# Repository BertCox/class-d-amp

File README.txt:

File: README.txt
Description: Project-specific instructions and information concerning files
    located within this hierarchy and subhierarchies. In the event of
    conflicts, the lowest-level README.txt file is used for information
    regarding a file or files.

Current Location: ClassDAmp/

Description:
    The Class-D Audio amplifier is an audio amplifier based on the 2004 Sorensen
audio amplifier design (http://listen.to/audioexperiment). The amplifier is able
to provide 100 watts RMS power spread across 2 stereo channels (50 watts RMS each)

Contents:
    Included in this repository are the source files and documentation
necessary to recreate the Class-D audio amplifier. If you believe something is 
missing from the project, please contact us at http://nbitwonder.com/blog/contact

Documentation:
    Documentation related to this project is included in the 'Documentation'
folder. For additional documentation and other information, please see:
http://nbitwonder.com/blog/projects/class-d-audio-amp/

License Information:
    NBitWonder projects are released under the GNU GPL v3.0 for software,
firmware, simulations, and documentation and Creative Commons CC-BY-3.0 
for electronics and mechanical components. License copies can be found in the
file 'license.txt' in each of these top-level folders.
    NBitWonder projects may use files, software, libraries, etc. which is not
open source. These components may not be distributed within the project
repository or use a different license than that specified in license.txt. In
these cases, acquisition instructions and license exceptions are noted in a
given hierarchy's 'README.txt' file. Where conflicting, the lowest-level
'README.txt' file shall apply to a given file or files.

Ben Laskowski
Chief Technical Officer
NBitWonder, LLC

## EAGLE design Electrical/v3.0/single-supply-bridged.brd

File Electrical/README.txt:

File: README.txt
Description: Project-specific instructions and information concerning files
    located within this hierarchy and subhierarchies. In the event of
    conflicts, the lowest-level README.txt file is used for information
    regarding a file or files.

Current Location: ClassDAmp/Electrical

Notes:
    This directory contains the following files:
    Version 3.0:
	* single-supply-bridged schematic and layout: The most recent version of 	  the circuit, and the only supported version.
    Version 2.0:
        * single-supply-bridged schematic and layout: 50W max output, questionable 	  speaker protection circuit
    Version 1.0:    
        * class-d-amp-single-supply schematic and pcb: An untested lower-output
          version, appx. 15W per channel
        * class-d-amp-3-5-mm sch/pcb: A dual-supply version, 25W per channel max.
          Not recommended for construction.
        * class-d-amp sch/pcb: The original board layout. Self-destructed during
          first test. Do not build.

Software:
    All electronic design files were created using EagleCAD v5.11 from CADSoft. 
A freeware copy of this software, as well as additional information about this 
software, can be found at http://www.cadsoftusa.com/

License:
    All electronic CAD design files contained within this hierarchy, except those
noted in the 'Exceptions' section below, are made publicly available via a 
Creative-Commons CC-BY-SA 3.0 license. For more information on the license, see 
http://creativecommons.org/licenses/by-sa/3.0/
    Additionally, a complete copy of the license text can be found in the file
'license.txt' distributed within this folder.

Exceptions:
    The following alternative licensing requirements apply to the following files:

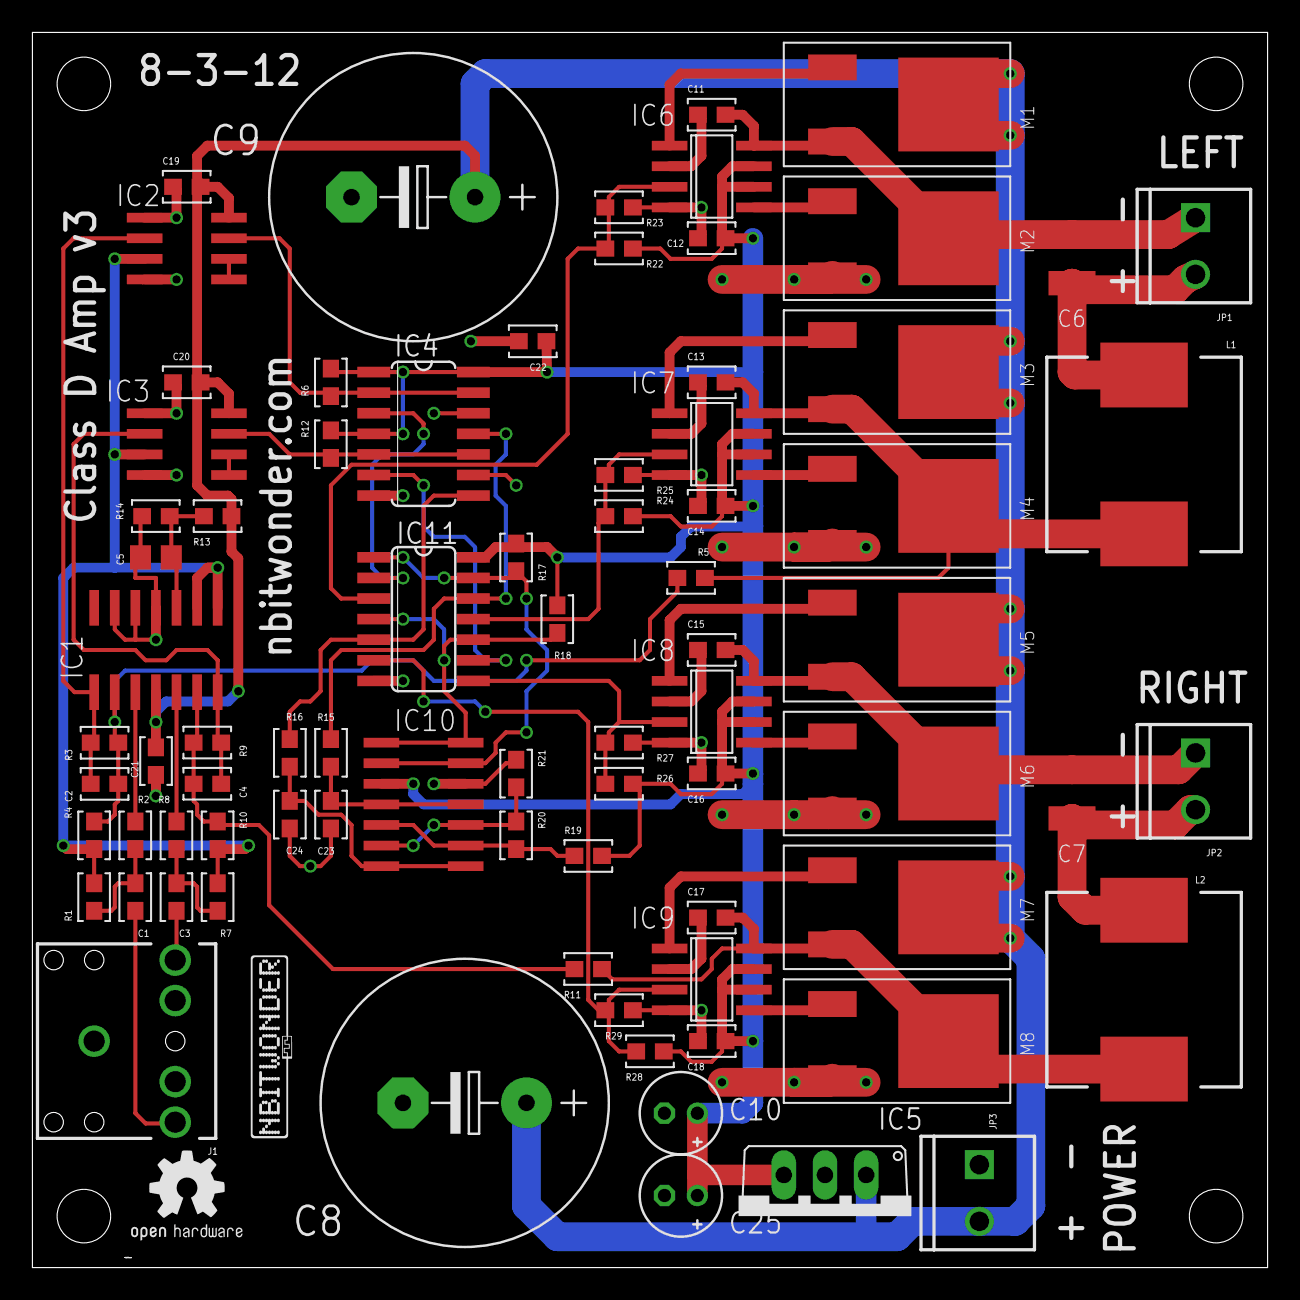
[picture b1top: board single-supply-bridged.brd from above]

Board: 2 copper layers, 76.2 x 76.2 mm, 85 parts (0 on the bottom side), 51 nets.

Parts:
C1, C3, C11, C13, C15, C17: 1u; 0603
C2, C4, C23, C24: 820p; 0603
C5: 10u; C0805
C6, C7: 270n; C1210K
C8, C9: 3300u; E7,5-18
C10, C25: 100u; E2-5
C12, C14, C16, C18, C19, C20, C21, C22: 100n; 0603
GOLD_ORB_SM1: OSHWLOGO_GOLD_ORB_SM; OSHW2
IC1: TL084D; SO14
IC2, IC3: LM311D; SO08
IC4: 74HC86D; SO14
IC5: 7805TV; TO220V
IC6, IC7, IC8, IC9: MCP14628; SO-08
IC10: LM339D; SO14
IC11: 74LS126D; SO14
J1: AUDIO-JACKPTH; AUDIO-JACK
JP1, JP2, JP3: SCREWTERMINAL-3.5MM-2
L1, L2: 33u; CDRH125
M1, M2, M3, M4, M5, M6, M7, M8: DMN4009LK3; TO252-3L
R1, R7: 15k; 0603
R2, R4, R8, R10, R13, R14, R19, R21, R22, R23, R24, R25, R26, R27, R28, R29: 2.2k; 0603
R3, R9: 1M; 0603
R5, R11, R20: 30k; 0603
R6, R12, R17, R18: 220; 0603
R15, R16: 10k; 0603
U$1, U$2, U$3, U$4: STAND-OFF
U$5: NBW_LOGOSMALL; NBW_LOGO

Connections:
+5V: C10.+, C12.2, C14.2, C16.2, C18.2, C22.1, C25.+, IC4.1, IC4.4, IC4.14, IC5.3, IC6.6, IC6.7, IC7.6, IC7.7, IC8.6, IC8.7, IC9.6, IC9.7, IC10.3, IC11.14, R6.2, R12.2, R17.2, R18.2, R19.1, R22.2, R24.2, R26.2, R28.2
+12V: C8.+, C9.+, C19.2, C20.2, C21.1, IC1.4, IC2.8, IC3.8, IC5.1, JP3.2, M1.2, M3.2, M5.2, M7.2, R13.2
DCLL: IC1.3, R2.2
DCLR: IC1.5, R8.2
GND: C5.2, C8.-, C9.-, C10.-, C12.1, C14.1, C16.1, C18.1, C19.1, C20.1, C21.2, C22.2, C23.2, C24.2, C25.-, IC1.11, IC1.12, IC1.13, IC2.1, IC2.4, IC3.1, IC3.4, IC4.7, IC4.9, IC4.12, IC5.2, IC6.4, IC7.4, IC8.4, IC9.4, IC10.12, IC11.7, J1.1, JP3.1, M2.3, M4.3, M6.3, M8.3, R14.1, R21.2, R23.2, R25.2, R27.2, R29.2
LGATE: IC10.2, IC10.13, IC11.1, IC11.13, R17.1
unnamed: C11.1, IC6.2
unnamed: C1.2, R1.1, R2.1
unnamed: C6.1, C11.2, IC6.8, JP1.1, M1.3, M2.2
unnamed: IC6.1, M1.1
unnamed: IC6.5, M2.1
unnamed: C13.2, IC7.8, L1.1, M3.3, M4.2, R5.2
unnamed: C13.1, IC7.2
unnamed: IC7.1, M3.1
unnamed: IC7.5, M4.1
unnamed: IC4.3, IC11.2
unnamed: C1.1, J1.5
unnamed: C15.1, IC8.2
unnamed: IC2.5, IC2.6
unnamed: IC8.1, M5.1
unnamed: IC8.5, M6.1
unnamed: IC6.3, IC11.3, R22.1, R23.1
unnamed: C3.1, J1.2
unnamed: C2.1, IC1.2, R3.1, R4.2, R5.1
unnamed: C2.2, IC1.1, IC2.2, R3.2
unnamed: C17.1, IC9.2
unnamed: C17.2, IC9.8, L2.1, M7.3, M8.2, R11.2
unnamed: IC9.1, M7.1
unnamed: IC9.5, M8.1
unnamed: C7.2, JP2.2, L2.2
unnamed: IC2.7, IC4.2, IC4.13, R6.1
unnamed: C6.2, JP1.2, L1.2
unnamed: C24.1, IC10.7, IC10.8, R16.2
unnamed: C23.1, IC10.4, IC10.11, R15.2
unnamed: IC3.5, IC3.6
unnamed: IC7.3, IC11.11, R24.1, R25.1
unnamed: IC3.7, IC4.5, IC4.10, R12.1
unnamed: C3.2, R7.1, R8.1
unnamed: IC8.3, IC11.8, R26.1, R27.1
unnamed: C4.1, IC1.6, R9.1, R10.2, R11.1
unnamed: C4.2, IC1.7, IC3.2, R9.2
unnamed: C7.1, C15.2, IC8.8, JP2.1, M5.3, M6.2
unnamed: IC4.6, IC11.9
unnamed: IC9.3, IC11.6, R28.1, R29.1
unnamed: C5.1, IC1.10, R13.1, R14.2
PWML: IC4.11, IC11.12, R15.1
PWMR: IC4.8, IC11.5, R16.1
RGATE: IC10.1, IC10.14, IC11.4, IC11.10, R18.1
VCCINT: IC1.8, IC1.9, IC2.3, IC3.3, R1.2, R4.1, R7.2, R10.1
VRHI: IC10.5, IC10.9, R19.2, R20.1
VRLO: IC10.6, IC10.10, R20.2, R21.1

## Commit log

2011-02-02 Added initial project notebook entries and initial schematics and PCB layouts
2011-02-02 Began project notebook
2011-02-02 Updated Readme file in root directory
2011-02-06 Updated 3.5mm input version to have bridging capability
2011-03-07 Updated the project notebook to reflect several recent prototype changes
2011-03-14 Updated project notebook and added preliminary schematic for single-supply version of the amplifier
2011-03-14 Added single-supply design files to repository
2011-03-15 Worked on component placement for single-supply amplifier
2011-03-15 Added tradeoff analysis to today's notebook entry
2011-03-19 Finished draft of non-bridged single supply version
2011-03-23 Project notebook updated to reflect tonight's prototype progress -- or lack thereof
2011-03-30 Fixed a few typos in the project notebook
2011-04-03 Updated notebook with single-supply bridged amplifier experiment descriptions
2011-04-05 Added noise suppression devices to comparator circuit -- PCB updates to follow
2011-04-07 Updated notebook with more experiment results and preliminary bridged single-supply layout
2011-04-08 Added measured values for circuit and inductor current analysis.
2011-04-08 Notebook updated with results of power supply loading experiment
2011-04-09 Tested with bigger inductor and updated notebook with results
2011-04-10 Added information on power supply shorting events and proposed solution
2011-04-10 Updated notebook with today's gating change experiment details
2011-04-14 Update notebook with believed solution to duty cycle and MOSFET drive problems
2011-04-27 Updated project notebook with preliminary results stemming from experiments with the new MCP14628 gate drivers
2011-04-30 Updated project notebook
2011-05-01 Finished updated single-supply bridged layout
2011-05-02 Finished PCB layout, awaiting peer review
2011-05-18 Updated notebook with results of new PCB build
2011-05-30 Updated a few resistor values in the schematic to improve low-frequency response
2011-06-21 Updated schematic for higher output power and better power supply rejection ratio
2011-06-22 Incremental updates -- changed C5 to 0805 package size, changed a few resistor values
2011-08-06 Tested performance enhancements and updated notebook
2011-08-07 Updated two component values, no other changes
2011-09-24 Added readme file to describe various project revisions in this directory
2011-09-25 Added BOM
2011-10-12 Repository structure cleanup, documentation overhaul
    LaTeX documentation replaced by OpenOffice
2012-06-05 Updated notebook with last weekend's development and testing activities
2012-08-19 Adding version 3.0 of circuit. New version features improved protective circuitry. Simulation of additions added. Notebook updated.
2012-08-22 Updated BOM
2012-08-23 Minor modifications to the v3.0 amplifier .brd file Added in George's Project Notebook
2012-08-23 Changed 74LS126 to 74HC126 in BOM
